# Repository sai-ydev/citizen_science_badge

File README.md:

# Citizen Science Badge

This repository contains all the hardware files, firmware for the Citizen Science Badge. A detailed write-up of this badge is available from [here](https://www.hackster.io/yamanoorsai/citizen-science-badge-c66165).

The badge consists of the following components:

* Raspberry Pi RP2040 microcontroller with 64MB flash.
* Invensense ICS-41350 MEMS Microphone. The audio captured from the microphone is used to detect sound using Edge Impulse
* Blues Wireless cellular module is used to upload data points to the cloud as well as receive "Save The Air" alerts from the cloud.
* Automotive Gauge Stepper Motor (x27.168) - Used to indicate measured air quality index.
* Bosch BMI270 IMU to detect motion
* DA7280 for haptic feedback
* BME688 air quality sensor to calculate air quality index as well as detect odors
* JST/ Qwiic sensor port for connecting external sensors.
* 3 x AA battery pack
* USB C port for programming.

## Firmware

Currently, the proof of concept has been implemented using Arduino. I plan to implement the code using the RP2040's C SDK. 

I have identified the following items as technical debt for this project.

* Implementing LED behavior for "Spare the Air" alerts
* The PCB design needs to be revised for low power operation
* The code needs to be re-written using the Pico C SDK
* Power profiling the badge

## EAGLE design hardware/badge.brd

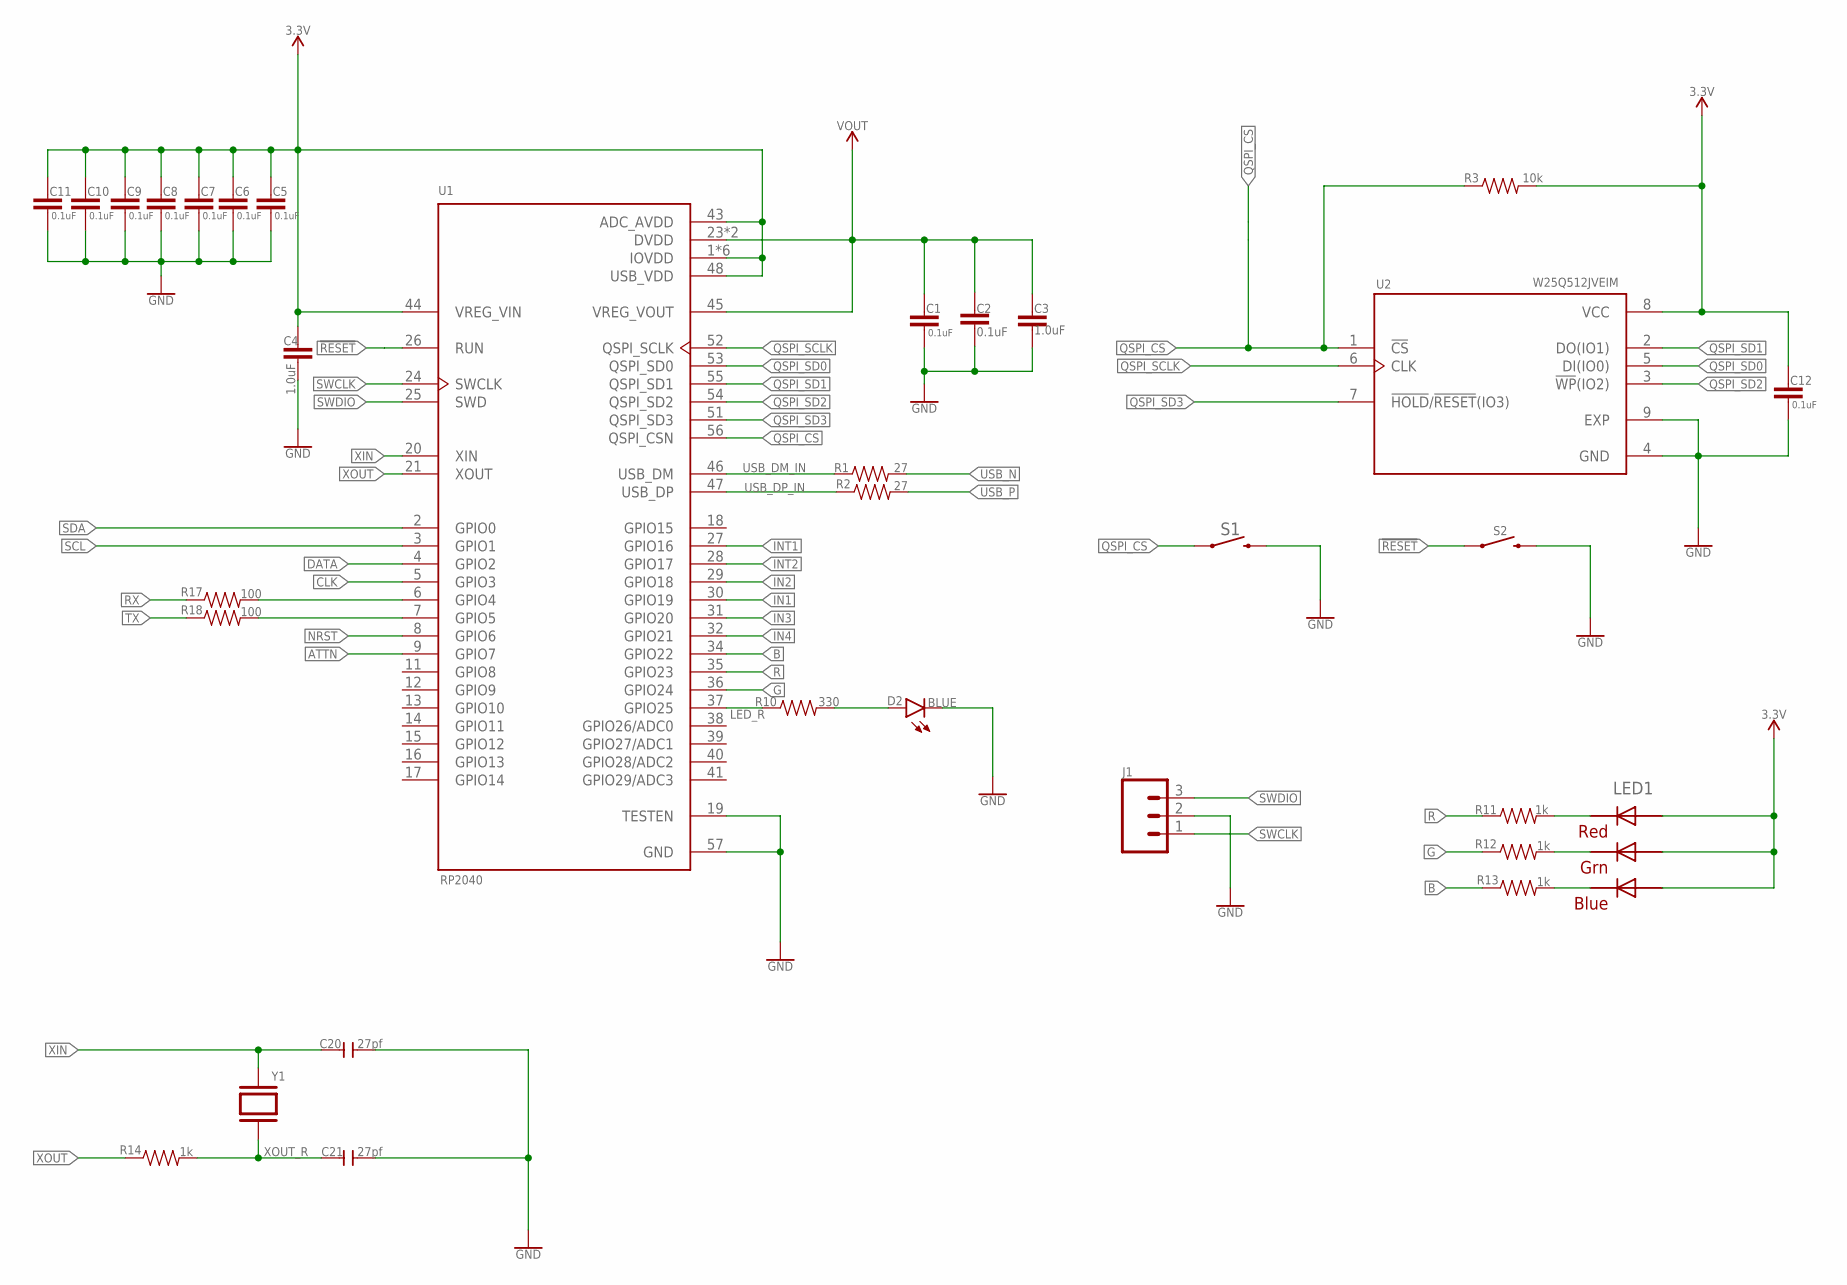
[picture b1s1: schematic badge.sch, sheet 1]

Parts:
C1, C2, C5, C6, C7, C8, C9, C10, C11, C12: 0.1uF; 0603
C3, C4: 1.0uF; 0603
C20, C21: 27pf; C0603
D2: BLUE; LED-0603
J1: CONN_03LONGPADS; 1X03_LONGPADS
LED1: RGBLED5050
R1, R2: 27; 0603
R3: 10k; 0603
R10: 330; 0603
R11, R12, R13, R14: 1k; 0603
R17, R18: 100; 0603
S1, S2: MOMENTARY-SWITCH-SPST-SMD-6.0X3.5MM; TACTILE_SWITCH_SMD_6.0X3.5MM
U1: RP2040; QFN40P700X700X90-57N
U2: W25Q512JVEIM; SON127P600X800X80-9N
Y1: ABLS-12.000MHZ-B4-T; XTAL_ABLS-12.000MHZ-B4-T

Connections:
3.3V: C4.1, C5.1, C6.1, C7.1, C8.1, C9.1, C10.1, C11.1, C12.1, LED1.1 (GREEN_A), LED1.2 (RED_A), LED1.3 (BLUE_A), R3.2, U1.1 (IOVDD), U1.10 (IOVDD), U1.22 (IOVDD), U1.33 (IOVDD), U1.42 (IOVDD), U1.43 (ADC_AVDD), U1.44 (VREG_VIN), U1.48 (USB_VDD), U1.49 (IOVDD), U2.8 (VCC); also elsewhere on the board
!RESET: S2.1, U1.26 (RUN)
ATTN: U1.9 (GPIO7); also elsewhere on the board
B: R13.1, U1.34 (GPIO22)
CLK: U1.5 (GPIO3); also elsewhere on the board
DATA: U1.4 (GPIO2); also elsewhere on the board
G: R12.1, U1.36 (GPIO24)
GND: C1.2, C2.2, C3.2, C4.2, C5.2, C6.2, C7.2, C8.2, C9.2, C10.2, C11.2, C12.2, C20.2, C21.2, D2.C, J1.2, S1.2, S2.2, U1.19 (TESTEN), U1.57 (GND), U2.4 (GND), U2.9 (EXP); also elsewhere on the board
IN1: U1.30 (GPIO19); also elsewhere on the board
IN2: U1.29 (GPIO18); also elsewhere on the board
IN3: U1.31 (GPIO20); also elsewhere on the board
IN4: U1.32 (GPIO21); also elsewhere on the board
INT1: U1.27 (GPIO16); also elsewhere on the board
INT2: U1.28 (GPIO17); also elsewhere on the board
LED_R: R10.1, U1.37 (GPIO25)
unnamed: D2.A, R10.2
unnamed: LED1.5 (RED_C), R11.2
unnamed: LED1.6 (GREEN_C), R12.2
unnamed: LED1.4 (BLUE_C), R13.2
unnamed: R17.2, U1.6 (GPIO4)
unnamed: R18.2, U1.7 (GPIO5)
NRST: U1.8 (GPIO6); also elsewhere on the board
QSPI_CS: R3.1, S1.1, U1.56 (QSPI_CSN), U2.1 (!CS)
QSPI_SCLK: U1.52 (QSPI_SCLK), U2.6 (CLK)
QSPI_SD0: U1.53 (QSPI_SD0), U2.5 (DI(IO0))
QSPI_SD1: U1.55 (QSPI_SD1), U2.2 (DO(IO1))
QSPI_SD2: U1.54 (QSPI_SD2), U2.3 (!WP!(IO2))
QSPI_SD3: U1.51 (QSPI_SD3), U2.7 (!HOLD!/!RESET!(IO3))
R: R11.1, U1.35 (GPIO23)
RX: R17.1; also elsewhere on the board
SCL: U1.3 (GPIO1); also elsewhere on the board
SDA: U1.2 (GPIO0); also elsewhere on the board
SWCLK: J1.1, U1.24 (SWCLK)
SWDIO: J1.3, U1.25 (SWD)
TX: R18.1; also elsewhere on the board
USB_DM_IN: R1.1, U1.46 (USB_DM)
USB_DP_IN: R2.1, U1.47 (USB_DP)
USB_N: R1.2; also elsewhere on the board
USB_P: R2.2; also elsewhere on the board
VOUT: C1.1, C2.1, C3.1, U1.23 (DVDD), U1.45 (VREG_VOUT), U1.50 (DVDD)
XIN: C20.1, U1.20 (XIN), Y1.2
XOUT: R14.1, U1.21 (XOUT)
XOUT_R: C21.1, R14.2, Y1.1

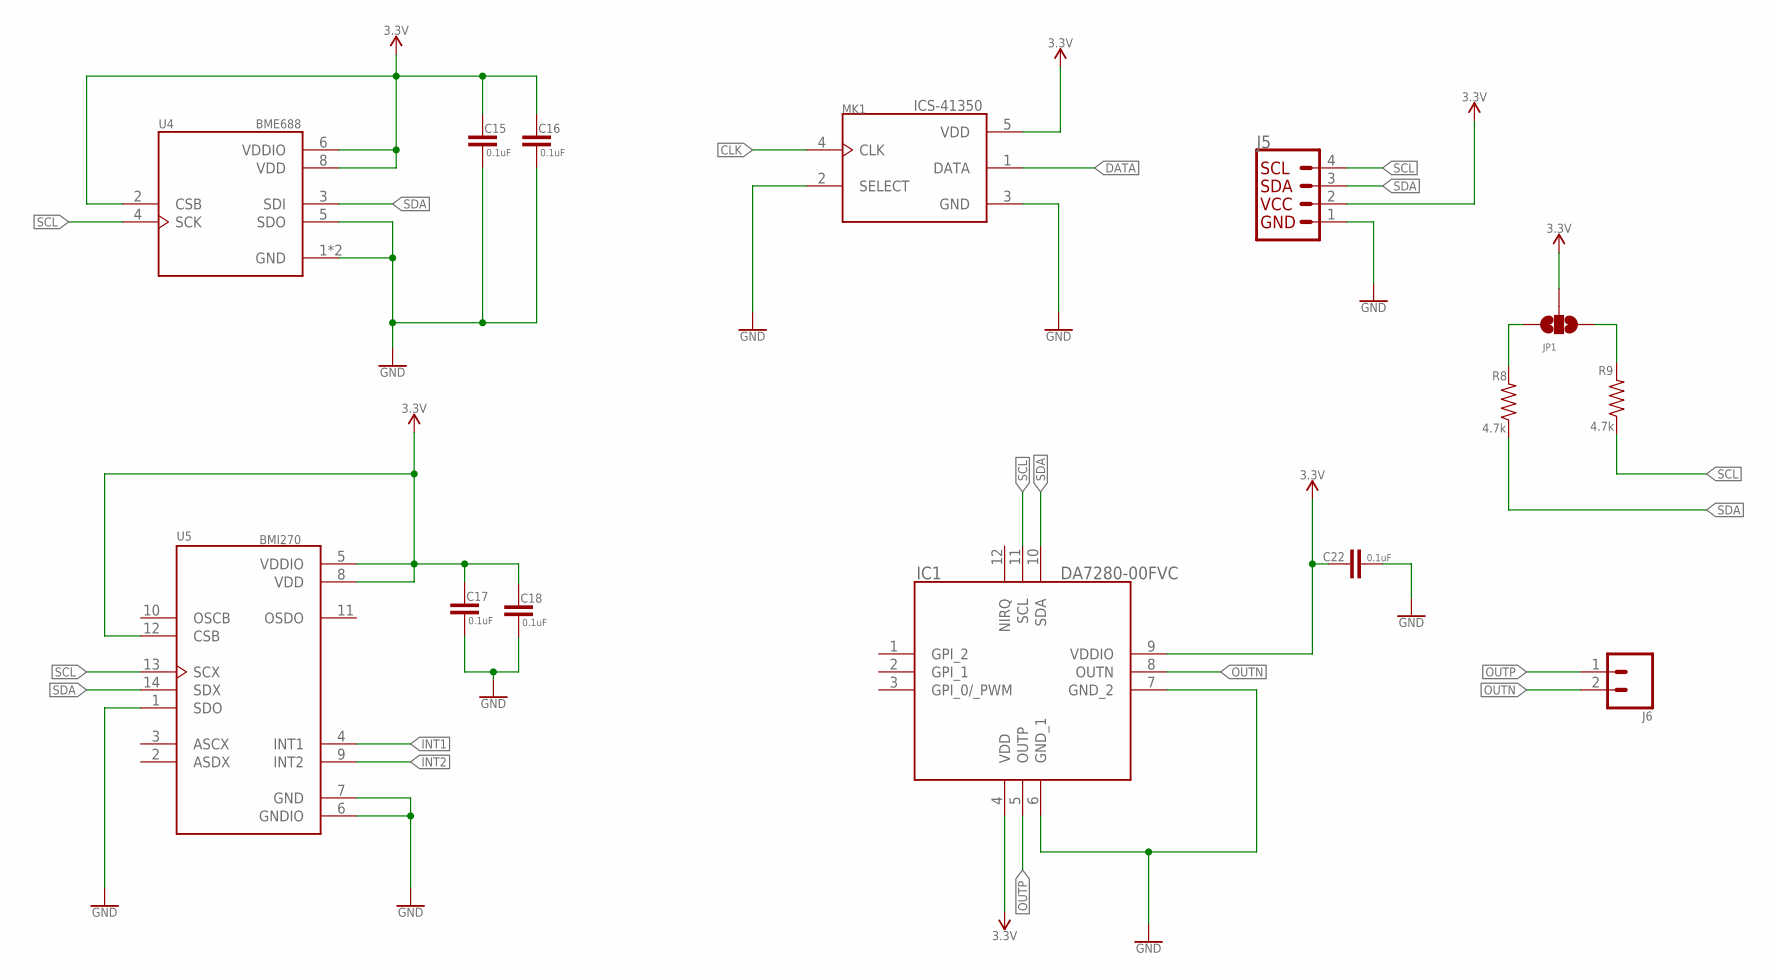
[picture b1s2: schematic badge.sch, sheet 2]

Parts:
C15, C16, C17, C18, C22: 0.1uF; 0603
IC1: DA7280-00FVC; QFN65P300X300X84-12N
J5: QWIIC_CONNECTORJS-1MM; 1X04_1MM_RA
J6: CONN_02; 1X02
JP1: JUMPER-SMT_3_NO_SILK; SMT-JUMPER_3_NO_SILK
MK1: ICS-41350; MIC_ICS-41350
R8, R9: 4.7k; 0603
U4: BME688; IC_BME688
U5: BMI270; XDCR_BMI270

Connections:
3.3V: C15.1, C16.1, C17.1, C18.1, C22.1, IC1.4 (VDD), IC1.9 (VDDIO), J5.2 (VCC), JP1.2, MK1.5 (VDD), U4.2 (CSB), U4.6 (VDDIO), U4.8 (VDD), U5.5 (VDDIO), U5.8 (VDD), U5.12 (CSB); also elsewhere on the board
CLK: MK1.4 (CLK); also elsewhere on the board
DATA: MK1.1 (DATA); also elsewhere on the board
GND: C15.2, C16.2, C17.2, C18.2, C22.2, IC1.6 (GND_1), IC1.7 (GND_2), J5.1 (GND), MK1.2 (SELECT), MK1.3 (GND), U4.1 (GND), U4.5 (SDO), U4.7 (GND), U5.1 (SDO), U5.6 (GNDIO), U5.7 (GND); also elsewhere on the board
INT1: U5.4 (INT1); also elsewhere on the board
INT2: U5.9 (INT2); also elsewhere on the board
unnamed: JP1.3, R8.2
unnamed: JP1.1, R9.2
OUTN: IC1.8 (OUTN), J6.2
OUTP: IC1.5 (OUTP), J6.1
SCL: IC1.11 (SCL), J5.4 (SCL), R9.1, U4.4 (SCK), U5.13 (SCX); also elsewhere on the board
SDA: IC1.10 (SDA), J5.3 (SDA), R8.1, U4.3 (SDI), U5.14 (SDX); also elsewhere on the board

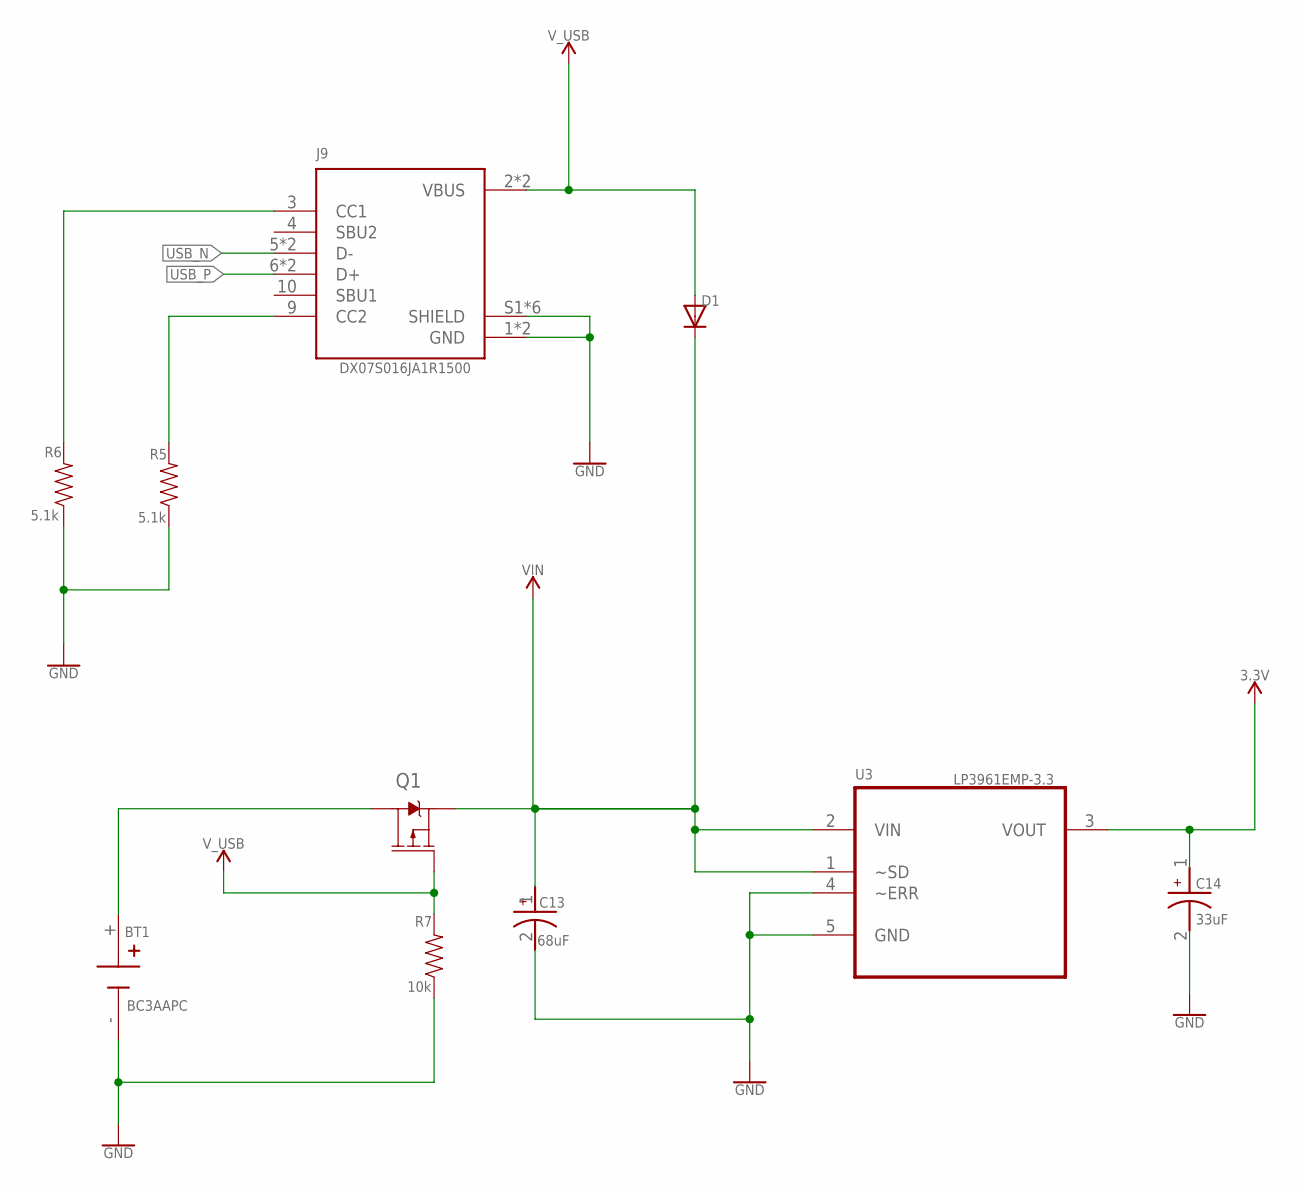
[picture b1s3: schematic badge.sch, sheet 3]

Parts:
BT1: BC3AAPC; BAT_BC3AAPC
C13: 68uF; CAPMP3216X180N
C14: 33uF; CAPMP3216X180N
D1: DIODESOD-123; SOD-123
J9: DX07S016JA1R1500; JAE_DX07S016JA1R1500
Q1: 2.5A/30V/105mΩ; SOT23-3
R5, R6: 5.1k; 0603
R7: 10k; 0603
U3: LP3961EMP-3.3; SOT150P696X180-5N

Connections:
3.3V: C14.1, U3.3 (VOUT); also elsewhere on the board
GND: BT1.-, C13.2, C14.2, J9.1 (GND), J9.12 (GND), J9.S1 (SHIELD), J9.S2 (SHIELD), J9.S3 (SHIELD), J9.S4 (SHIELD), J9.S5 (SHIELD), J9.S6 (SHIELD), R5.1, R6.1, R7.1, U3.4 (~ERR), U3.5 (GND); also elsewhere on the board
unnamed: BT1.+, Q1.3 (D)
unnamed: J9.3 (CC1), R6.2
unnamed: J9.9 (CC2), R5.2
USB_N: J9.5 (D-), J9.8 (D-); also elsewhere on the board
USB_P: J9.6 (D+), J9.7 (D+); also elsewhere on the board
VIN: C13.1, D1.C, Q1.2 (S), U3.1 (~SD), U3.2 (VIN); also elsewhere on the board
V_USB: D1.A, J9.2 (VBUS), J9.11 (VBUS), Q1.1 (G), R7.2

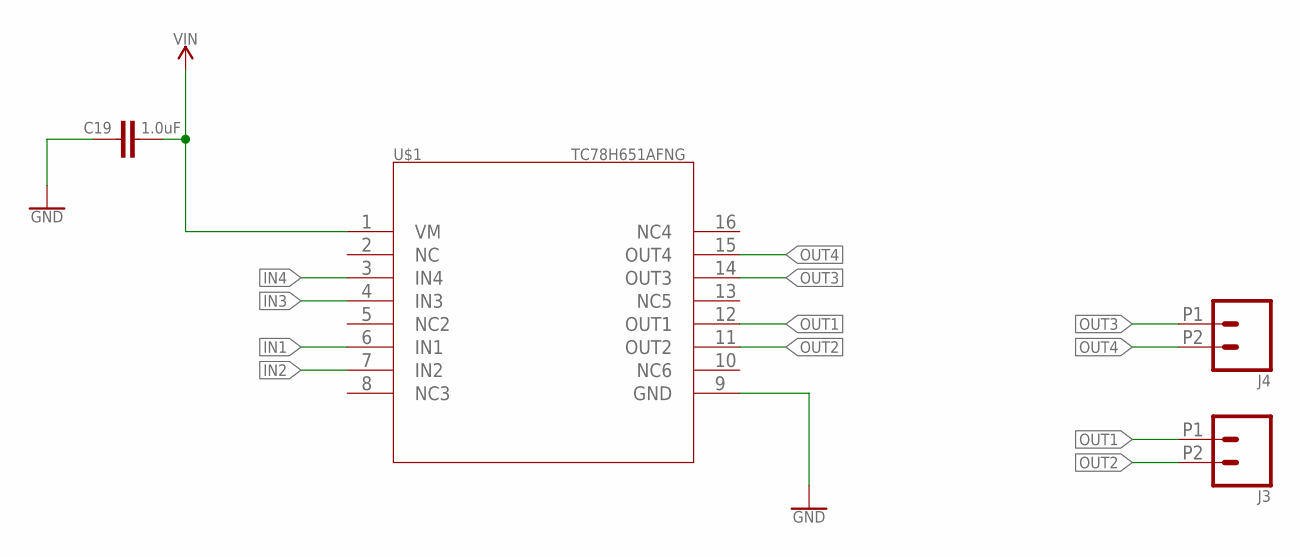
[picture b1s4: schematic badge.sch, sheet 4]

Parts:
C19: 1.0uF; 0603
J3, J4: CONN_022.54MM_SCREWTERM; 1X02_2.54_SCREWTERM
U$1: TC78H651AFNG; P-TSSOP16-0505-0.65-001

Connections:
GND: C19.1, U$1.9 (GND); also elsewhere on the board
IN1: U$1.6 (IN1); also elsewhere on the board
IN2: U$1.7 (IN2); also elsewhere on the board
IN3: U$1.4 (IN3); also elsewhere on the board
IN4: U$1.3 (IN4); also elsewhere on the board
OUT1: J3.P1 (1), U$1.12 (OUT1)
OUT2: J3.P2 (2), U$1.11 (OUT2)
OUT3: J4.P1 (1), U$1.14 (OUT3)
OUT4: J4.P2 (2), U$1.15 (OUT4)
VIN: C19.2, U$1.1 (VM); also elsewhere on the board

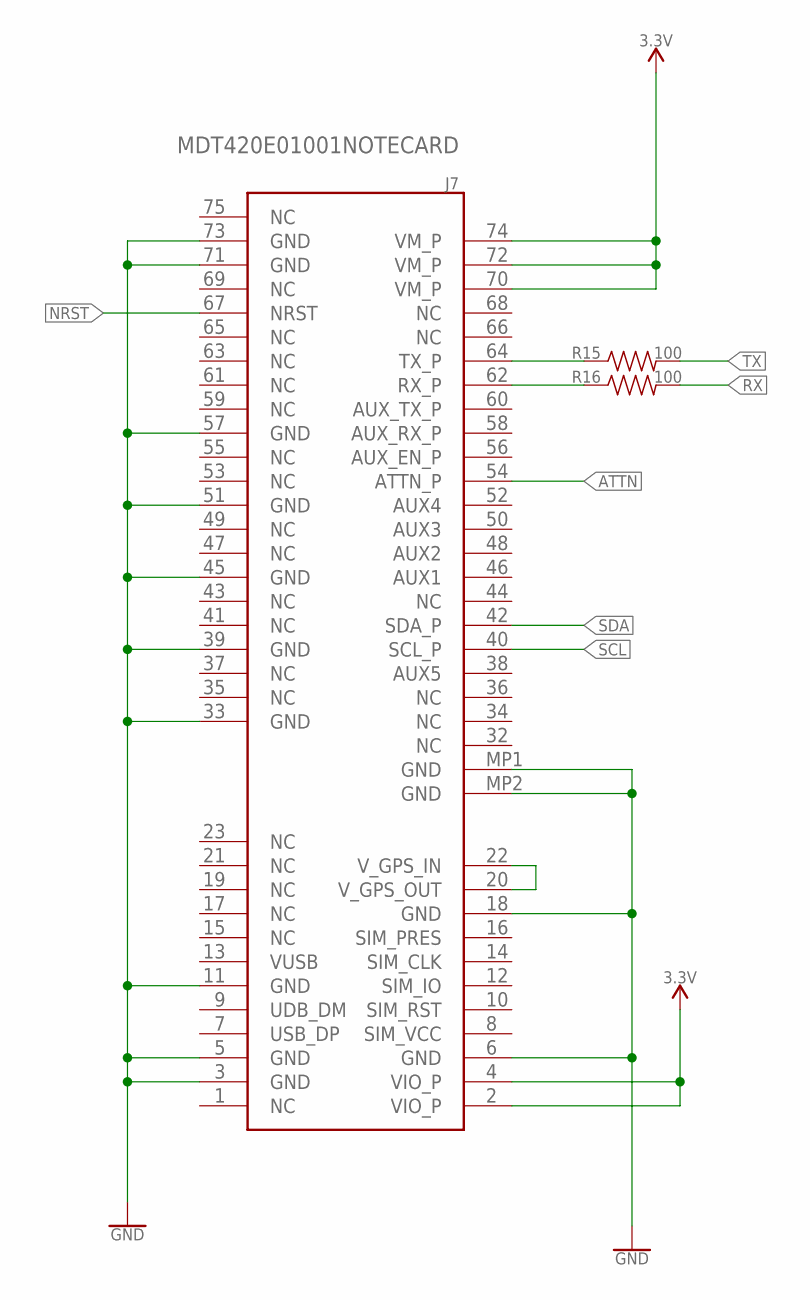
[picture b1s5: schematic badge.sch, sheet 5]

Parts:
J7: MDT420E01001NOTECARD; NOTECARD
R15, R16: 100; 0603

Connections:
3.3V: J7.2 (VIO_P), J7.4 (VIO_P), J7.70 (VM_P), J7.72 (VM_P), J7.74 (VM_P); also elsewhere on the board
ATTN: J7.54 (ATTN_P); also elsewhere on the board
GND: J7.3 (GND), J7.5 (GND), J7.6 (GND), J7.11 (GND), J7.18 (GND), J7.33 (GND), J7.39 (GND), J7.45 (GND), J7.51 (GND), J7.57 (GND), J7.71 (GND), J7.73 (GND), J7.MP1 (GND), J7.MP2 (GND); also elsewhere on the board
unnamed: J7.64 (TX_P), R15.1
unnamed: J7.62 (RX_P), R16.1
unnamed: J7.20 (V_GPS_OUT), J7.22 (V_GPS_IN)
NRST: J7.67 (NRST); also elsewhere on the board
RX: R16.2; also elsewhere on the board
SCL: J7.40 (SCL_P); also elsewhere on the board
SDA: J7.42 (SDA_P); also elsewhere on the board
TX: R15.2; also elsewhere on the board

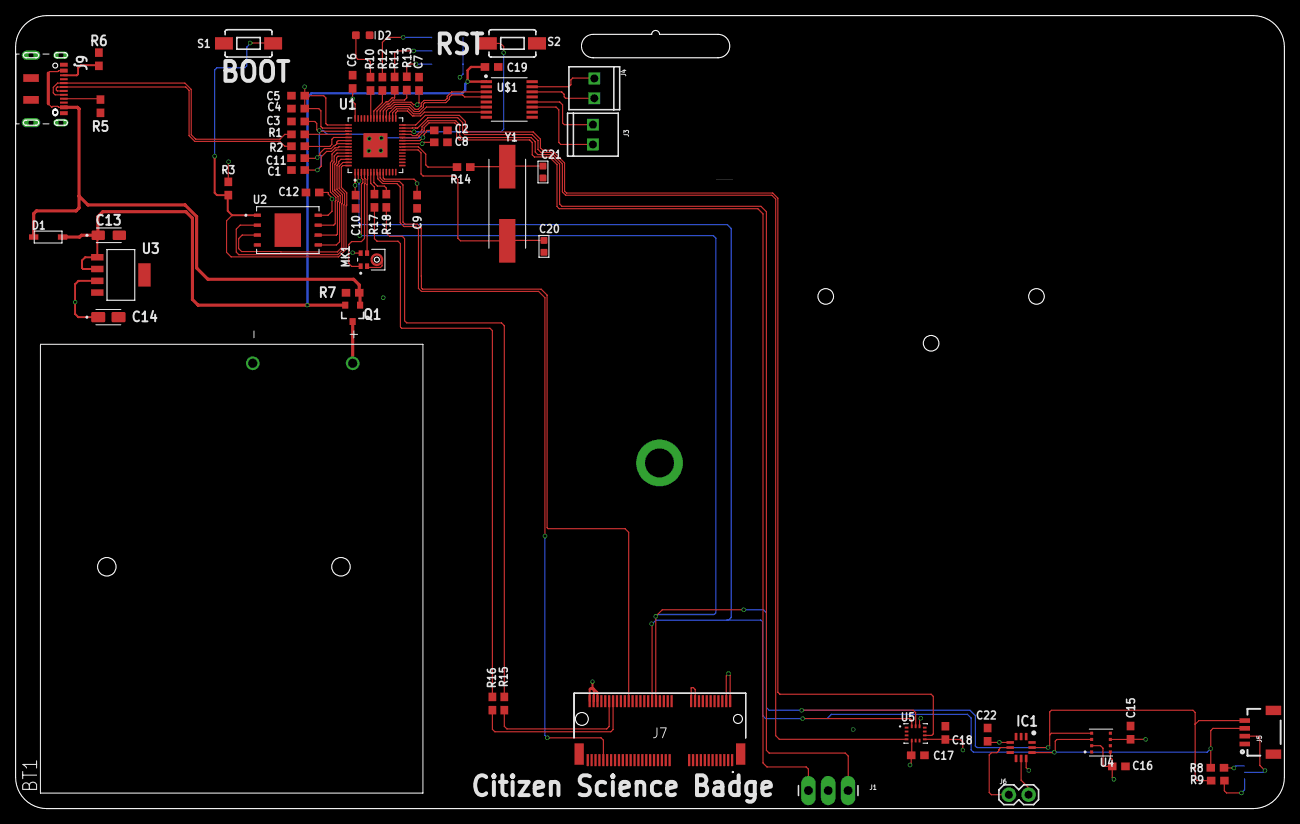
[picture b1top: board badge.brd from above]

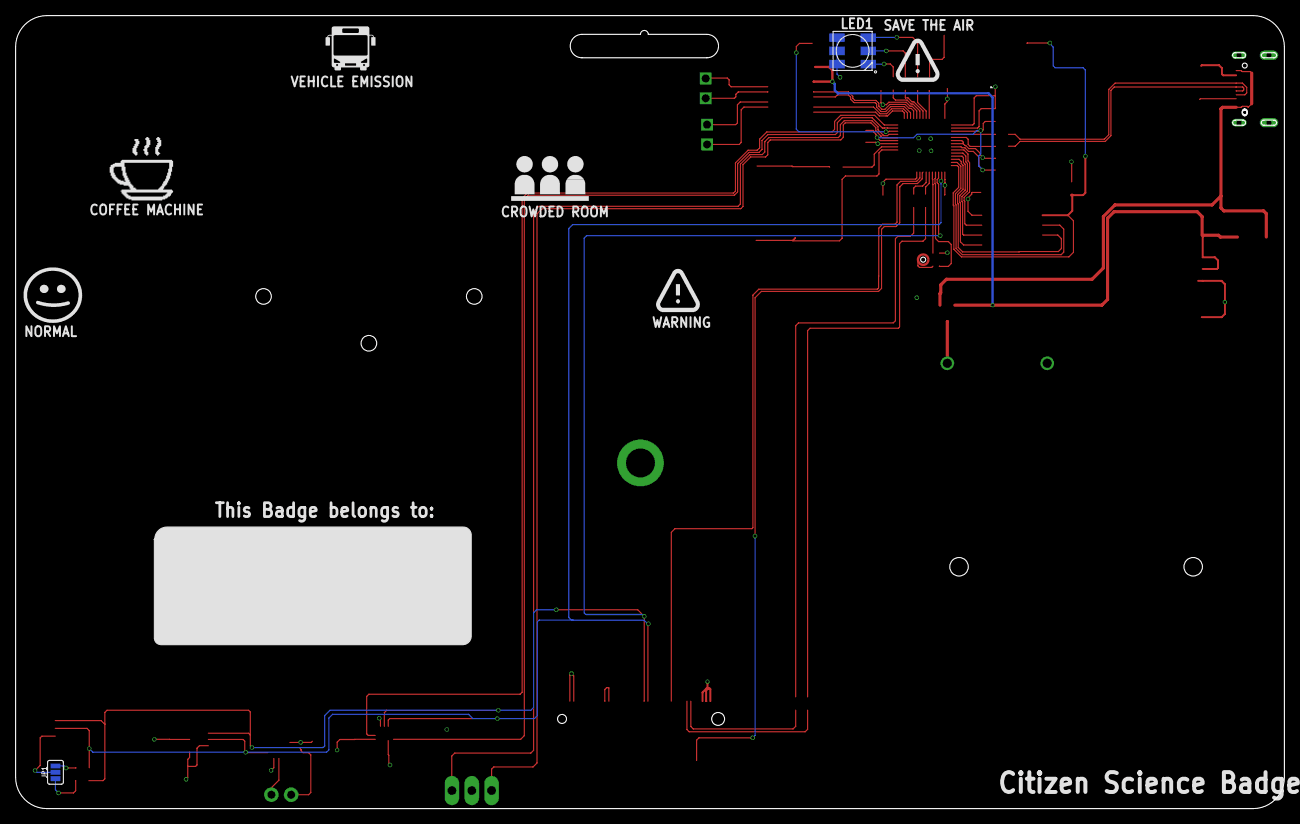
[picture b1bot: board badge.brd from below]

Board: 4 copper layers, 162.6 x 101.6 mm, 63 parts (2 on the bottom side), 59 nets.

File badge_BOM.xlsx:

Part | Value | Description | MPN | Remarks
BT1 | BC3AAPC | BC3AAPC | BC3AAPC | Do not Fit
C1, C2, C5, C6, C7, C8, C9, C10, C11, C12, C15, C16, C17, C18, C22 | 0.1uF | CAP CER 0.1UF 25V X7R 0603 | C0603C104K3RAC7867
C3, C4, C19 | 1.0uF | CAP CER 1UF 50V X5R 0603 | GRT188R61H105KE13D
C13 | 68uF | CAP TANT 68UF 20% 6.3V 1206 | T491A686M006AT
C14 | 33uF | CAP TANT 33UF 10% 6.3V 1206 | TAJA336K006RNJ
C20, C21 | 27pf | CAP CER 27PF 50V C0G 0603 | CGA3E2C0G1H270J080AA
D1 | 600 mV @ 200 mA | DIODE SCHOTTKY 30V 350MA SOD123 | SD103BWHE3-TP
D2 | BLUE | LED BLUE 0603 SMD | 5973604507F
IC1 | DA7280-00FVC | LRA/ERM HAPTIC DRIVER WLCSP15 | DA7280-00FVC
J1 |  | CONN_03LONGPADS | DNF
J3 |  | CONN_022.54MM_SCREWTERM | DNF
J4 |  | CONN_022.54MM_SCREWTERM | DNF
J5 |  | CONN HEADER SMD R/A 4POS 1MM | SM04B-SRSS-TB(LF)(SN)
J6 |  | CONN_02 | DNF
J7 | MDT420E01001 | CONN M.2 FMALE 67POS 0.020 GOLD | MDT420E01001
J9 | DX07S016JA1R1500 | CONN RCP USB2.0 TYP C 24P SMD RA | DX07S016JA1R1500
JP1 | JUMPER-SMT_3_NO_SILK | JUMPER-SMT_3_NO_SILK | DNF
LED1 | RGBLED5050 | RGB LED | DNF
MK1 | ICS-41350 | MICROPHONE MEMS DIGITAL PDM OMNI | ICS-41350
Q1 | 2.5A/30V/105mÎ© | MOSFET P-CH 30V 2.5A SOT-23 | DMG2307L-7
R1, R2 | 27 | RES 27 OHM 1% 1/10W 0603 | MCT06030C2709FP500
R3, R7 | 10k | RES 10K OHM 1% 1/10W 0603 | MCT06030C1002FPW00
R4, R11, R12, R13, R14 | 1k | RES 1K OHM 1% 1/8W 0603 | RNCP0603FTD1K00
R5, R6 | 5.1k | RES 5.1K OHM 5% 1/10W 0603 | RMCF0603JT5K10
R8, R9 | 4.7k | RES 4.7K OHM 0.5% 1/10W 0603 | MCT0603MD4701DP500
R10 | 330 | RES 330 OHM 5% 1/10W 0603 | RMCF0603JT330R
R15, R16, R17, R18 | 100 | RES 100 OHMS 0.1% 0.15W 0603 | RQ73C1J100RBTD
S1, S2 | MOMENTARY-SWITCH-SPST-SMD-6.0X3.5MM | TACT 6.0 X 3.5, 4.3 MM H, 130GF, | PTS636 SL43 SMTR LFS
U$1 | TC78H651AFNG | BRUSHED DC MOTOR DRIVER, DUAL-CH | TC78H651AFNG,EL
U1 | RP2040 | RP2040 | SC0914(7) (RP2040)
U2 | W25Q512JVEIM | W25Q512JVEIM | GD25S512MDYIGR
U3 | LP3961EMP-3.3 | IC REG LIN 3.3V 800MA SOT223-5 | LP3961EMP-3.3/NOPB
U4 | BME688 | SENSOR RH PRESSURE TEMP VOC | BME688
U5 | BMI270 | IMU ACCEL/GYRO I2C/SPI 14LGA | BMI270
Y1 | ABLS-12.000MHZ-B4-T | CRYSTAL 12.0000MHZ 18PF SMD | ABLS-12.000MHZ-B4-T

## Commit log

2023-01-24 Design files
2023-01-26 Arduino code check-in
2023-01-27 file re-org
2023-01-31 Checking master BoM
2023-01-31 files check-in
2023-04-07 hardware changes
2023-05-10 ieee paper

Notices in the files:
parts and their libraries:
SparkFun-Capacitors: Licensing: Creative Commons ShareAlike 4.0 International - https://creativecommons.org/licenses/by-sa/4.0
